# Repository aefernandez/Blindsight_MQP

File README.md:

# Blindsight MQP

This repository hosts the code for the Blindsight MQP '19. Blindsight is an assistive navigation for the blind. It uses ultrasonic sensors mounted on a pair of 3D printed glasses to detect head-level objects. The device communicates with two vibrating modules using Nordic Semi NRF24 communication modules. The vibrating modules are wrist-worn devices that contain vibrating motors to give an indication of the distance to nearby obstacles. 

MQP - Major Qualifying Project 
Worcester Polytechnic Institute (WPI)

## Getting Started

Visit the Blindsight website and follow the instructions to get started on building your own prototype.

### Prerequisites

In order to program your prototype you'll need to install the Arduino IDE and drivers. The code is written for the ATmega328 platform (UNO, Nano, Mini).

### Installing

Upon downloading the files, place the Blindsight_Library folder inside the Arduino->libraries folder. This will install the Blindsight_Library in your Arduino environment. 

## Authors

* Alan Fernandez      - aefernandez@wpi.edu
* Aatreya Chakravarti - achakravarti@wpi.edu

## License

This project is licensed under the MIT License - see the [LICENSE.md](LICENSE.md) file for details

## Acknowledgments

* Professor Stephen J. Bitar
* Petra Hartman

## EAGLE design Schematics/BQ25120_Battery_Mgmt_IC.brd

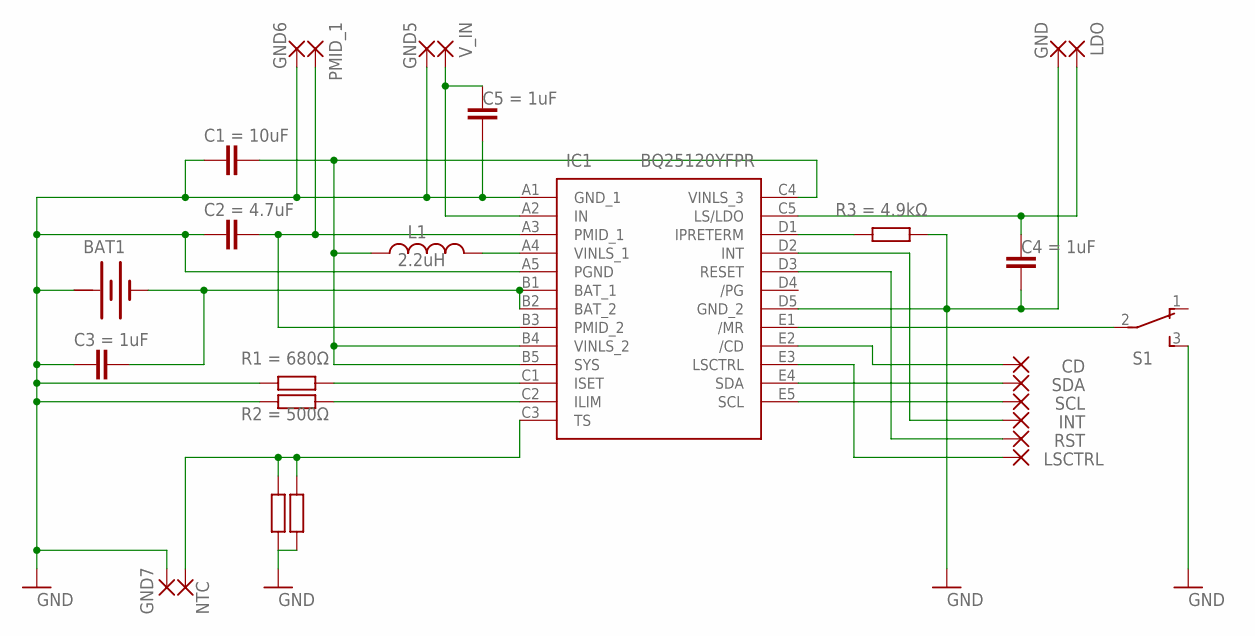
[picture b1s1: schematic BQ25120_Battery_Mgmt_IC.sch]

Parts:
BAT1: BATTERY
CD: SMD2; SMD1,27-2,54
GND, GND5, GND6, GND7: SMD2; SMD1,27-2,54
IC1: BQ25120YFPR; BGA25C40P5X5_247X253X50
INT: SMD2; SMD1,27-2,54
L1: L-USL2012C; L2012C
LDO: SMD2; SMD1,27-2,54
LSCTRL: SMD2; SMD1,27-2,54
NTC: SMD2; SMD1,27-2,54
PMID_1: SMD2; SMD1,27-2,54
RST: SMD2; SMD1,27-2,54
S1: TL36PO; TL3XPO
SCL: SMD2; SMD1,27-2,54
SDA: SMD2; SMD1,27-2,54
V_IN: SMD2; SMD1,27-2,54

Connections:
+: BAT1.+@1 (+)
GND: BAT1.+, GND.1, GND5.1, GND6.1, GND7.1, IC1.A1 (GND_1), IC1.A5 (PGND), IC1.D5 (GND_2), S1.3 (S)
unnamed: IC1.A4 (VINLS_1), L1.2
unnamed: IC1.E1 (/MR), S1.2
unnamed: BAT1.-, IC1.B1 (BAT_1), IC1.B2 (BAT_2)
unnamed: IC1.B4 (VINLS_2), IC1.B5 (SYS), IC1.C4 (VINLS_3), L1.1
unnamed: IC1.A2 (IN), V_IN.1
unnamed: CD.1, IC1.E2 (/CD)
unnamed: IC1.E4 (SDA), SDA.1
unnamed: IC1.E5 (SCL), SCL.1
unnamed: IC1.D2 (INT), INT.1
unnamed: IC1.D3 (RESET), RST.1
unnamed: IC1.E3 (LSCTRL), LSCTRL.1
unnamed: IC1.C5 (LS/LDO), LDO.1
unnamed: IC1.C3 (TS), NTC.1
unnamed: IC1.A3 (PMID_1), IC1.B3 (PMID_2), PMID_1.1

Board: 2 copper layers, 18 parts (0 on the bottom side), 15 nets, no tracks yet.

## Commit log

2018-11-12 Ultrasonic V1
    Arduino code for the ultrasonic version of the Blindsight MQP. This version contains working code to poll the ultrasonic sensors and untested code for temperature compensation as well as vibrating mo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
2018-11-12 BQ25120 Circuit
    First rendition of the BQ25120 schematic. The PCB is not ready in this version.
2018-11-13 Added netlist
2018-11-28 BQ51013a Altium Files
    Schematic mostly completed.
2018-12-07 vl53l0x code
    vl53l0x arduino mega code
2018-12-07 vl53l0x code
    instantiate new objects for each sensor
2018-12-08 vl53lox.ino
    Move mesureSens variables to globals
2018-12-11 Ultrasonic Library
    Added the library for the ultrasonic sensors. It contains the functions to handle both the ultrasonic sensor specific tasks and the general Blindsight tasks.
2018-12-11 Receiver Module Code
    First iteration of the receiver module code. It implements the necessary code to communicate with the NRF24L01. This code is untested.
2018-12-12 Updated Main Code w/ NRF24L01
    Added necessary code to communicate with modules via NRF24L01. The communications part is untested.
2018-12-12 Compensated Ultrasonic Code
    Compensation of sensorList[] function done
2018-12-13 Vibration Intensity Buckets Added
    Added vibration intensity buckets to the code. The buckets are set for demo meaning that the ranges they group are much shorter than necessary for real world operation.
2018-12-13 Temperature Based Recalibration Implemented
    This version includes the necessary code for temperature recalibration.
2018-12-13 Sensor Power MOSFET Added
    This version contains the necessary code to switch off the sensors during temperature calibration.
2018-12-14 Schematics and Code Updates
    Minor updates in the code. Mostly formatting. Schematics for the B Term report were added.
2018-12-16 Original GIT Schematics
    Schematics for originally-selected power modules
2019-01-12 Motor_PWM_Testing
    Single motor testing with different pwm duty cycles via a potentiometer
2019-01-24 Sleep Mode, Updated Libraries
    Additions:
    -Master waits for slaves to report before allowing the device to begin working
    -Push button on master triggers sleep mode on slaves and master
    -Slaves enter sleep mode with timeout. Poll every 8s for wake up signal.
    Notes:
    -Sleep mode in the master remains untested.
2019-01-27 Sleep Mode Master Fixes
    Fixed bug that kept master from waking up from sleep mode. A print statement inside the PAUSE_ISR seems to have been the culprit.
2019-01-28 Updated Readme
    Added content to the readme file
2019-01-28 Comments, Formatting...
    Added comments, fixed formatting, made code generally prettier.
2019-01-28 Added Acknowledgements
2019-03-21 Improvements
    This version removes the lag between sensing an object and vibrating the bands. The lag is resolved by manually triggering each sensor rather than depending on the automatic triggering offered by the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
2019-04-05 Intensity Adjustment Friendliness
    The device now vibrates constantly while the intensity is being adjusted. This allows for the user to more easily select the desired intensity level.
2019-04-05 Intensity Adjustment Friendliness
    The device now vibrates constantly while the intensity is being adjusted. This allows for the user to more easily select the desired vibration intensity.
2019-04-10 Removed Irrelevant Testing Code
    Removed sample test code for the TOF sensor.
2019-04-10 Repository Cleanup
    Removed imcomplete testing codes and old schematics and renamed files for consistency.
